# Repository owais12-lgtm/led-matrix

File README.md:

# LED-matrix 

This is a through-hole LED matrix display made with a Pro Micro and a buncha leds! This matrix is pretty useful for small animations. . It is also made to fit on small circuit boards

# Features

- THT LEDs for ease of soldering!
- Made with a Pro Micro
- 6 x 6 matrix
- 36 LEDs!

# schematic

# PCB

# 3d render

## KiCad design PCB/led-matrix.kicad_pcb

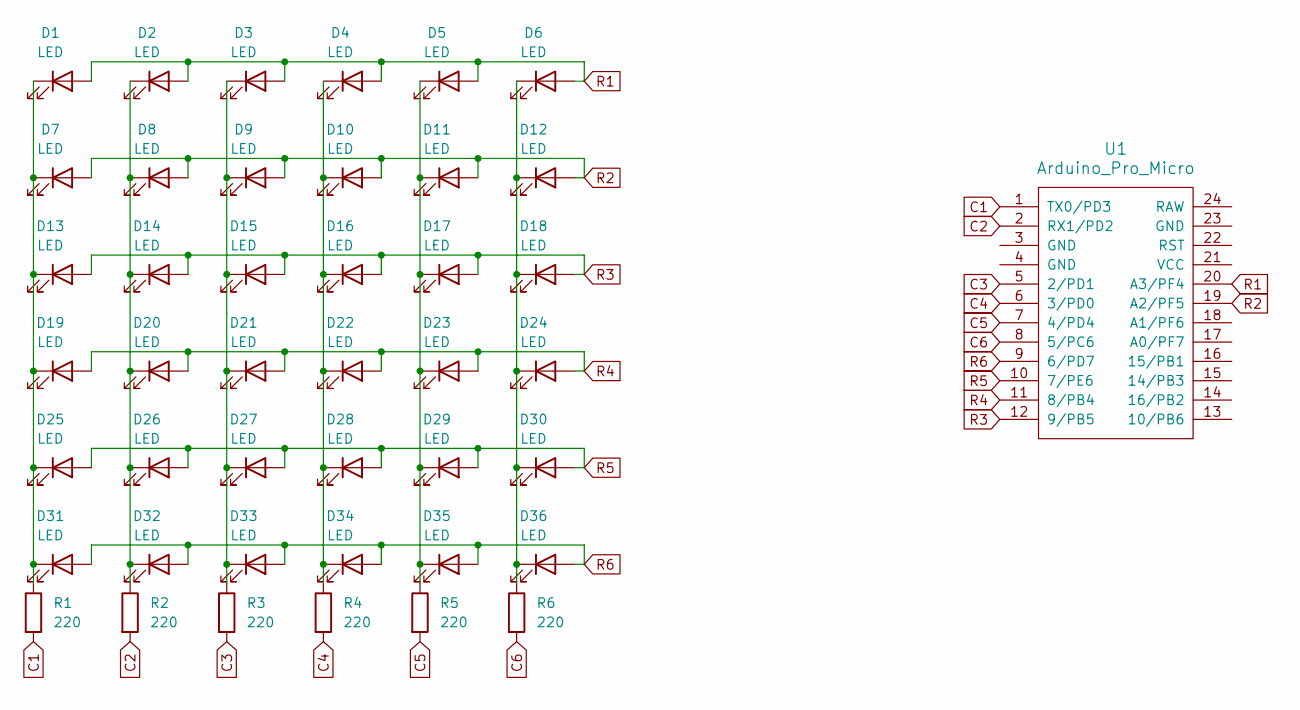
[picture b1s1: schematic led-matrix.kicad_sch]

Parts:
D1, D2, D3, D4, D5, D6, D7, D8, D9, D10, D11, D12, D13, D14, D15, D16, D17, D18, D19, D20, D21, D22, D23, D24, D25, D26, D27, D28, D29, D30, D31, D32, D33, D34, D35, D36: LED; LED_D3.0mm
R1, R2, R3, R4, R5, R6: 220; R_Axial_DIN0207_L6.3mm_D2.5mm_P7.62mm_Horizontal
U1: Arduino_Pro_Micro

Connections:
C1: R1.2, U1.1 (TX0/PD3)
C2: R2.2, U1.2 (RX1/PD2)
C3: R3.2, U1.5 (2/PD1)
C4: R4.2, U1.6 (3/PD0)
C5: R5.2, U1.7 (4/PD4)
C6: R6.2, U1.8 (5/PC6)
unnamed: D1.1 (K), D7.1 (K), D13.1 (K), D19.1 (K), D25.1 (K), D31.1 (K), R1.1
unnamed: D4.1 (K), D10.1 (K), D16.1 (K), D22.1 (K), D28.1 (K), D34.1 (K), R4.1
unnamed: D5.1 (K), D11.1 (K), D17.1 (K), D23.1 (K), D29.1 (K), D35.1 (K), R5.1
unnamed: D6.1 (K), D12.1 (K), D18.1 (K), D24.1 (K), D30.1 (K), D36.1 (K), R6.1
unnamed: D2.1 (K), D8.1 (K), D14.1 (K), D20.1 (K), D26.1 (K), D32.1 (K), R2.1
unnamed: D3.1 (K), D9.1 (K), D15.1 (K), D21.1 (K), D27.1 (K), D33.1 (K), R3.1
R1: D1.2 (A), D2.2 (A), D3.2 (A), D4.2 (A), D5.2 (A), D6.2 (A), U1.20 (A3/PF4)
R2: D7.2 (A), D8.2 (A), D9.2 (A), D10.2 (A), D11.2 (A), D12.2 (A), U1.19 (A2/PF5)
R3: D13.2 (A), D14.2 (A), D15.2 (A), D16.2 (A), D17.2 (A), D18.2 (A), U1.12 (9/PB5)
R4: D19.2 (A), D20.2 (A), D21.2 (A), D22.2 (A), D23.2 (A), D24.2 (A), U1.11 (8/PB4)
R5: D25.2 (A), D26.2 (A), D27.2 (A), D28.2 (A), D29.2 (A), D30.2 (A), U1.10 (7/PE6)
R6: D31.2 (A), D32.2 (A), D33.2 (A), D34.2 (A), D35.2 (A), D36.2 (A), U1.9 (6/PD7)

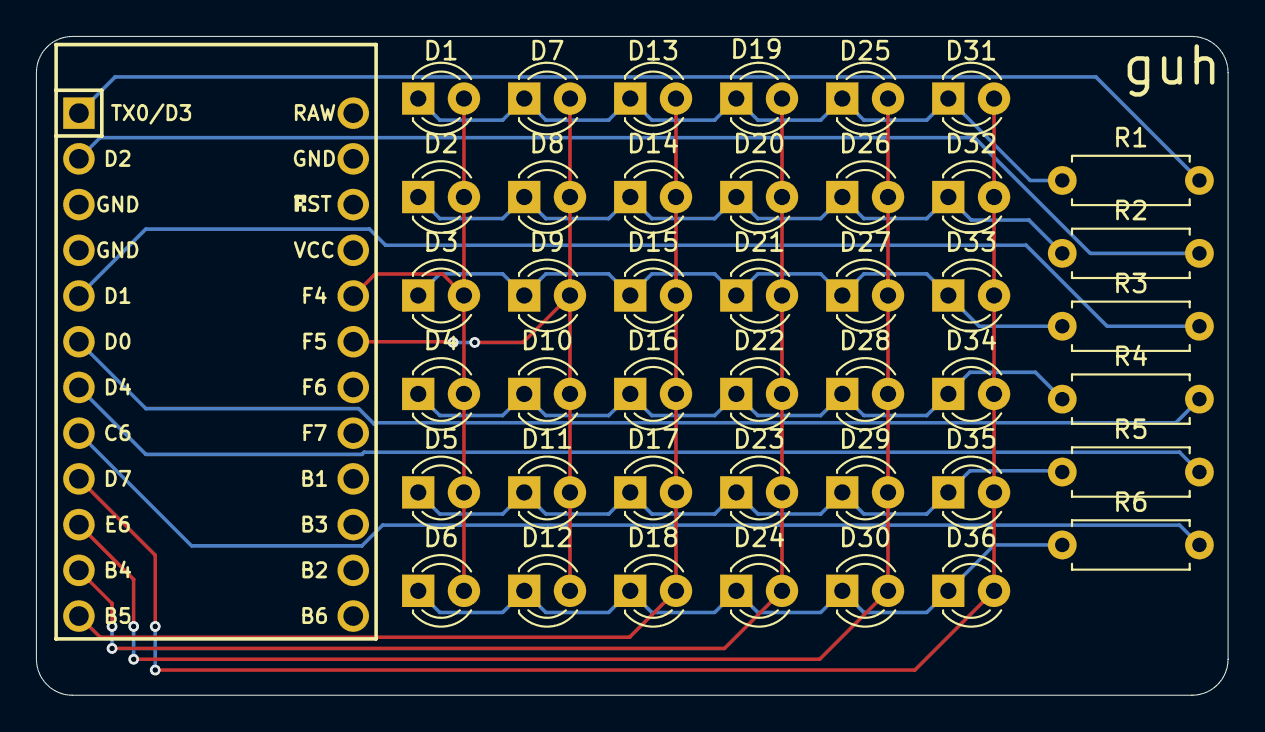
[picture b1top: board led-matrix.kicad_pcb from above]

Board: 2 copper layers, 66.2 x 36.6 mm, 43 parts (0 on the bottom side), 18 nets.
